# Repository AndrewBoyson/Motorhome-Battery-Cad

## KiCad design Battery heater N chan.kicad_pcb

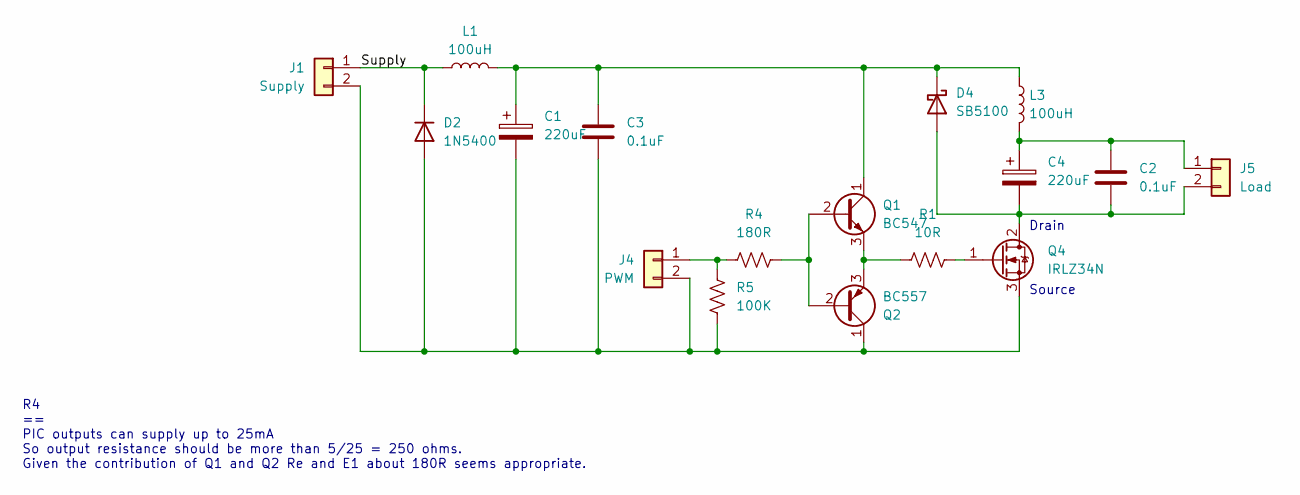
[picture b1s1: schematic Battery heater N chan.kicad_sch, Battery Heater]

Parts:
C1, C4: 220uF; CP_Radial_D5.0mm_P2.50mm
C2, C3: 0.1uF; C_Rect_L9.0mm_W4.0mm_P7.50mm_MKT
D2: 1N5400; D_DO-201AD_P15.24mm_Horizontal
D4: SB5100; D_DO-15_P15.24mm_Horizontal
J1: Supply; JST_EH_B2B-EH-A_1x02_P2.50mm_Vertical
J4: PWM; JST_EH_B2B-EH-A_1x02_P2.50mm_Vertical
J5: Load; JST_EH_B2B-EH-A_1x02_P2.50mm_Vertical
L1, L3: 100uH; L_Toroid_Vertical_L22.4mm_W10.2mm_P7.90mm_Vishay_TJ4
Q1: BC547; TO-92_Inline
Q2: BC557; TO-92_Inline
Q4: IRLZ34N; TO-220-3_Vertical
R1: 10R; R_Axial_DIN0204_L3.6mm_D1.6mm_P7.62mm_Horizontal
R4: 180R; R_Axial_DIN0204_L3.6mm_D1.6mm_P7.62mm_Horizontal
R5: 100K; R_Axial_DIN0204_L3.6mm_D1.6mm_P7.62mm_Horizontal

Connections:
/Supply: D2.1 (K), J1.1, L1.1
unnamed: C1.2, C3.2, D2.2 (A), J1.2, J4.2, Q2.1 (C), Q4.3 (S), R5.2
unnamed: C2.2, C4.2, D4.2 (A), J5.2, Q4.2 (D)
unnamed: C1.1, C3.1, D4.1 (K), L1.2, L3.1, Q1.1 (C)
unnamed: J4.1, R4.1, R5.1
unnamed: C2.1, C4.1, J5.1, L3.2
unnamed: Q1.2 (B), Q2.2 (B), R4.2
unnamed: Q1.3 (E), Q2.3 (E), R1.1
unnamed: Q4.1 (G), R1.2

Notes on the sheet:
Drain
Source
R4 == PIC outputs can supply up to 25mA So output resistance should be more than 5/25 = 250 ohms. Given the contribution of Q1 and Q2 Re and E1 about 180R seems appropriate.

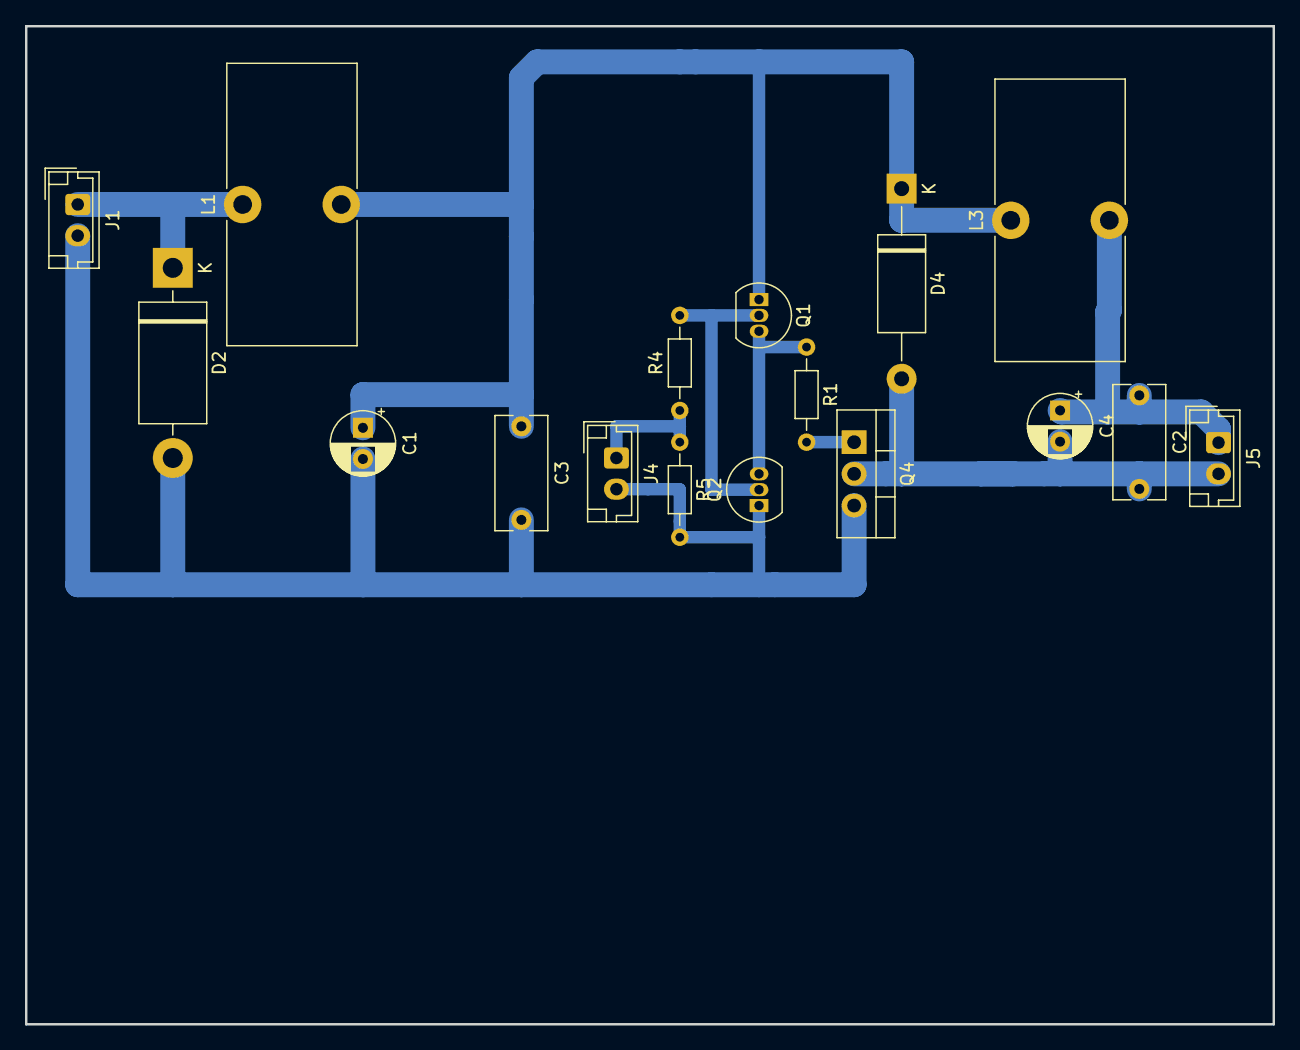
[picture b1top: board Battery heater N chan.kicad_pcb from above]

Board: 2 copper layers, 100.0 x 80.0 mm, 17 parts (0 on the bottom side), 9 nets.
